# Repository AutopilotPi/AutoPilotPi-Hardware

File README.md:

# [ENGLISH](https://github.com/Ncerzzk/AutoPilotPi-Hardware/blob/master/README_EN.md)
# AutoPilotPi-Hardware

AutoPilotPi 是一个能够运行 PX4 等自动驾驶固件的单板计算机(SBC)。与通用的 SBC（如树莓派）不同，AutoPilotPi 集成了多种传感器（IMU、磁罗盘、气压计等），因此无需额外的接线即可使用，对于微型飞行器和电路洁癖患者来说非常友好。

AutoPilotPi 使用 V3s 处理器，虽然 V3s 不是性能强大的处理器，但如果能够证明 PX4 能在这些性能较弱的 Linux 处理器上运行，则对于性能更强的处理器来说更加不在话下了。

与传统基于 MCU 的自动驾驶固件不同，使用 Linux 系统的优势在于支持更多的开发语言和工具链，可以更方便地进行二次开发和调试。同时，开启了软实时后的内核基本可以满足 PX4 的实时性要求。

## 接口与传感器

- ICM20600：六轴惯性测量单元
- QMC5883L：三轴磁罗盘
- SPL06：气压高度传感器
- 3 个串口(U0、U1、U2，其中 U0 用于 Linux 调试)
- 1 个 I2C 接口
- 1 个 SPI 接口
- 最多 9 个 PWM 通道

## 特点

- 封装对手焊友好 (EQFP-128)
- 内置 DRAM
- 价格较为便宜

## 相关项目

- V3s 的 Linux 内核：https://github.com/Ncerzzk/linux
- 使用该项目的四旋翼飞行器 (WIP)：https://github.com/Ncerzzk/V3s_Quadrotor
- 该项目的 PX4 分支（部分提交尚未被官方 PX4 接受）：https://github.com/Ncerzzk/PX4-Autopilot
- FPGA 的 HDL 代码：https://github.com/Ncerzzk/I2C_PWM
- Wiki：https://github.com/Ncerzzk/AutoPilotPi-Hardware/wiki

## Images

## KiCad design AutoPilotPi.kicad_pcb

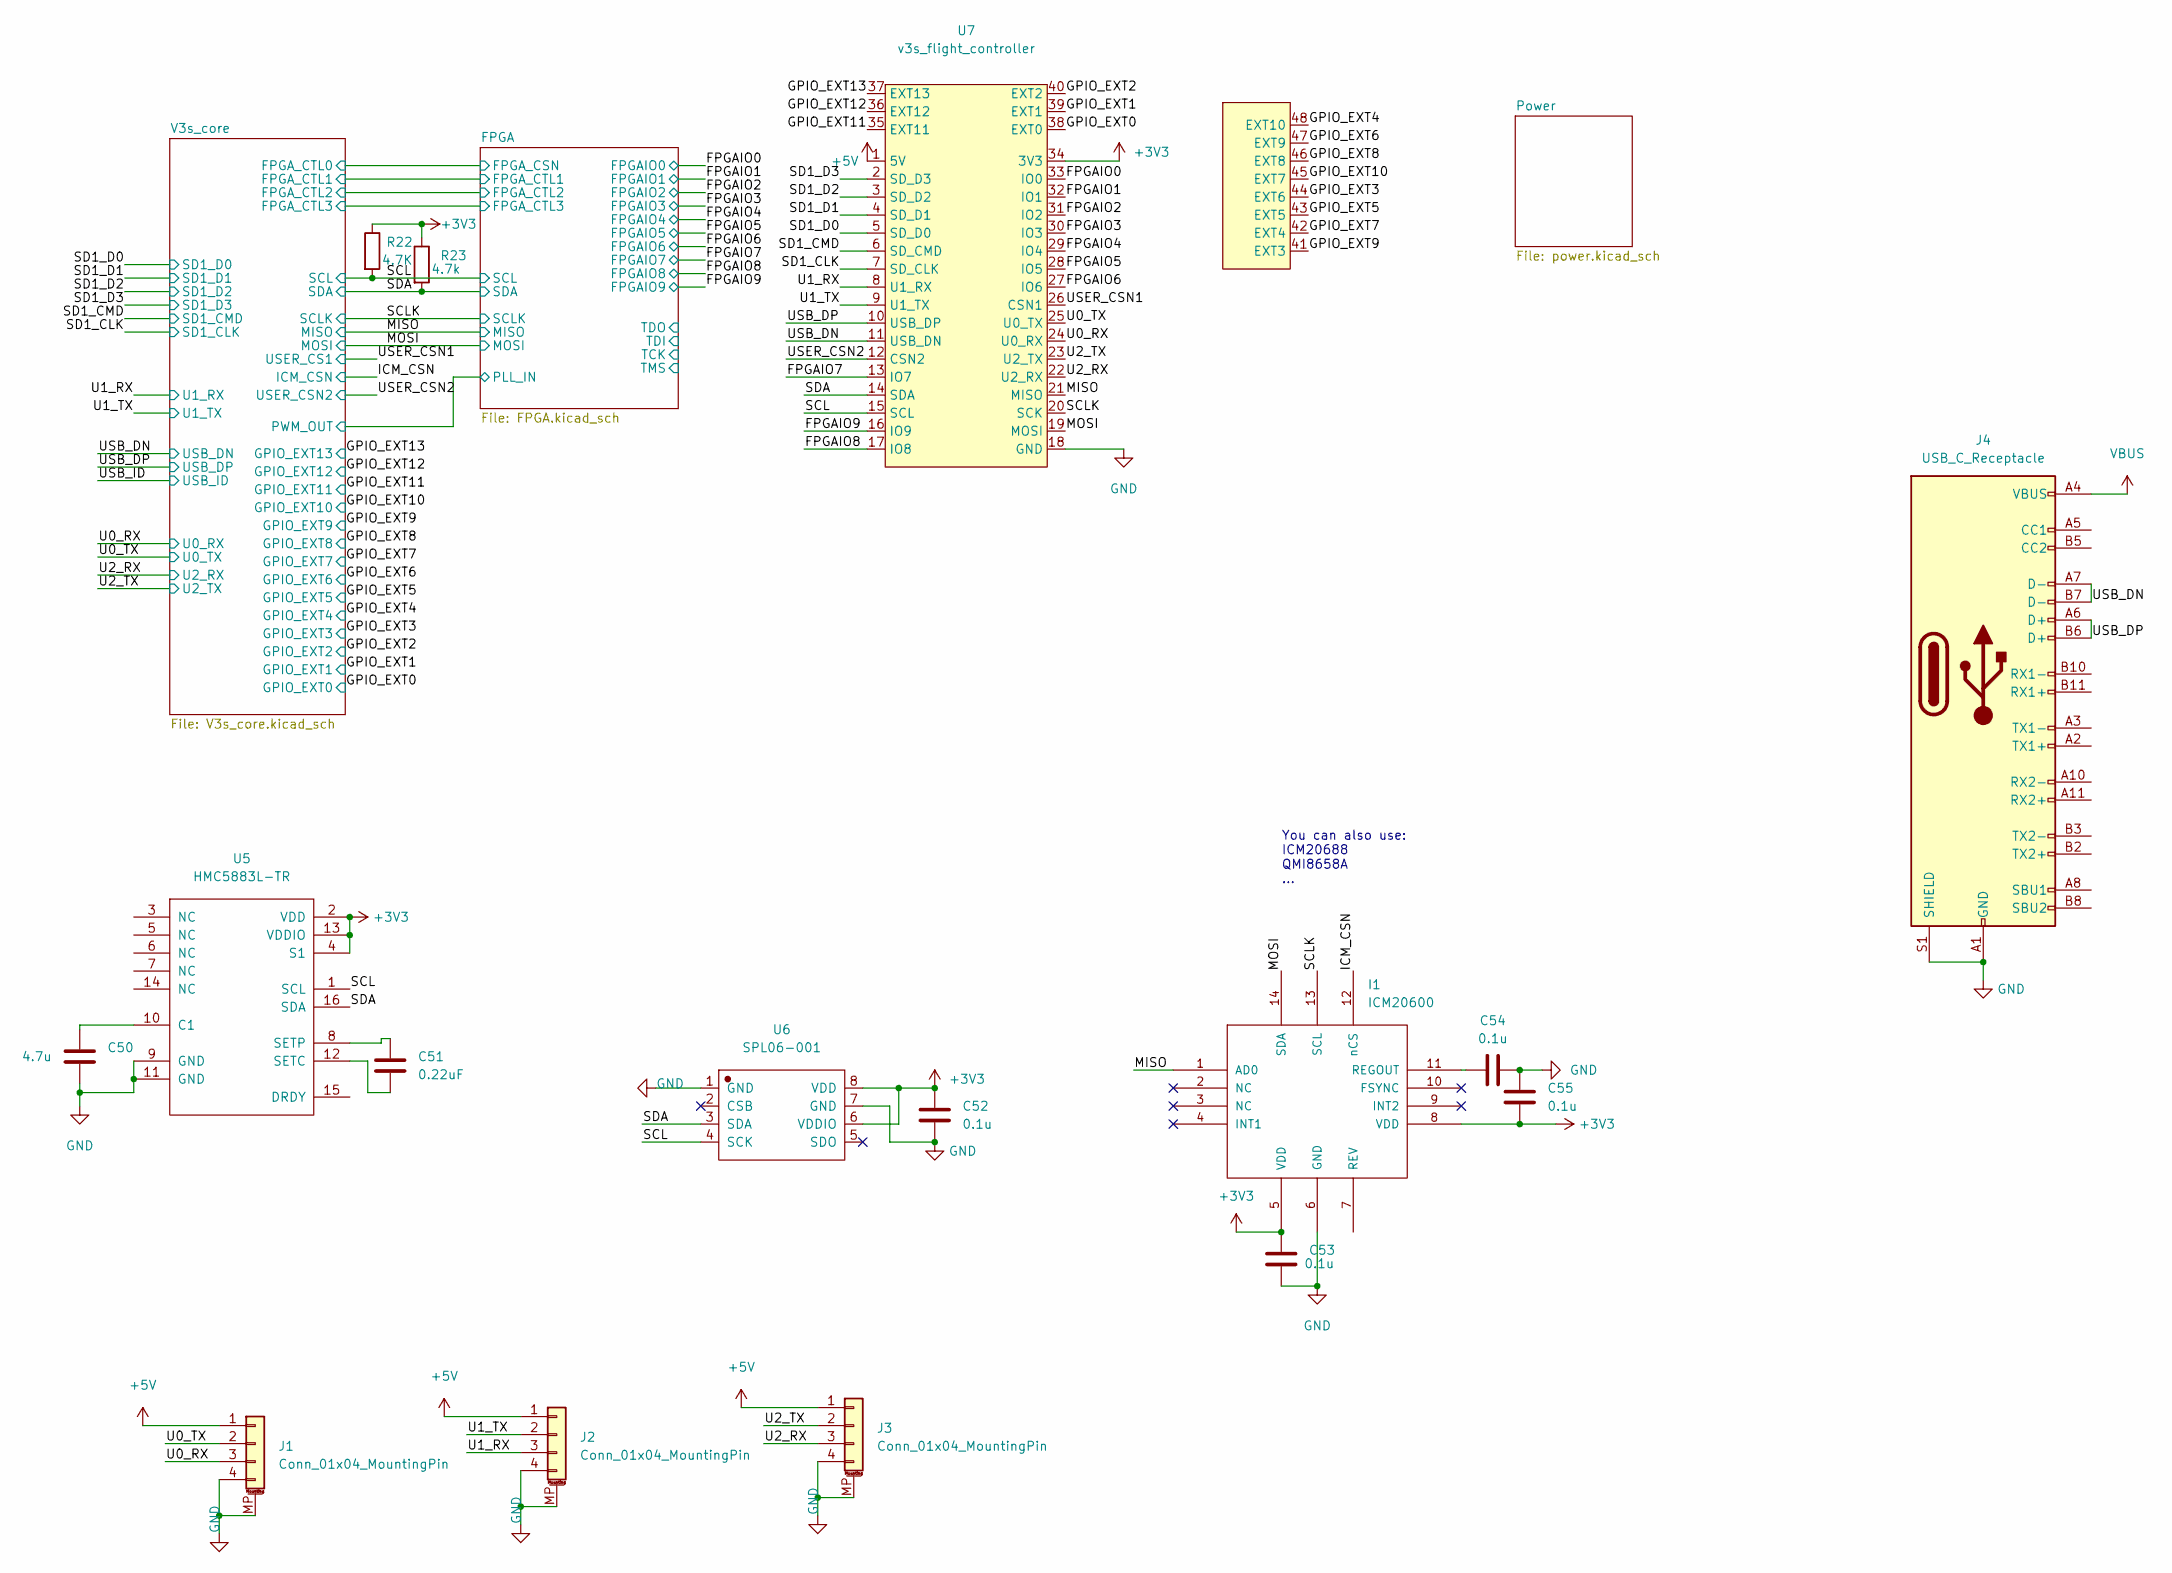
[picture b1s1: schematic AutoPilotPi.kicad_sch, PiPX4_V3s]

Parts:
C50: 4.7u; C_0402_1005Metric
C51: 0.22uF; C_0402_1005Metric
C52, C53, C54, C55: 0.1u; C_0402_1005Metric
I1: ICM20600; Bosch_LGA-14_3x2.5mm_P0.5mm
J1, J2, J3: Conn_01x04_MountingPin; Molex_CLIK-Mate_502382-0470_1x04-1MP_P1.25mm_Vertical
J4: USB_C_Receptacle; USB_C_Receptacle_Palconn_UTC16-G
R22: 4.7K; R_0402_1005Metric
R23: 4.7k; R_0402_1005Metric
U5: HMC5883L-TR; LGA-16_3x3mm_P0.5mm
U6: SPL06-001; Bosch_LGA-8_2x2.5mm_P0.65mm_ClockwisePinNumbering
U7: v3s_flight_controller; Flight_Core

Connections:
+3V3: C52.1, C53.2, C55.2, I1.5 (VDD), I1.8 (VDD), R22.1, R23.1, U5.2 (VDD), U5.4 (S1), U5.13 (VDDIO), U6.6 (VDDIO), U6.8 (VDD), U7.34 (3V3); also elsewhere on the board
+5V: J1.1, J2.1, J3.1, U7.1 (5V); also elsewhere on the board
/FPGAIO0: U7.33 (IO0); also elsewhere on the board
/FPGAIO1: U7.32 (IO1); also elsewhere on the board
/FPGAIO2: U7.31 (IO2); also elsewhere on the board
/FPGAIO3: U7.30 (IO3); also elsewhere on the board
/FPGAIO4: U7.29 (IO4); also elsewhere on the board
/FPGAIO5: U7.28 (IO5); also elsewhere on the board
/FPGAIO6: U7.27 (IO6); also elsewhere on the board
/FPGAIO7: U7.13 (IO7); also elsewhere on the board
/FPGAIO8: U7.17 (IO8); also elsewhere on the board
/FPGAIO9: U7.16 (IO9); also elsewhere on the board
/GPIO_EXT0: U7.38 (EXT0); also elsewhere on the board
/GPIO_EXT1: U7.39 (EXT1); also elsewhere on the board
/GPIO_EXT2: U7.40 (EXT2); also elsewhere on the board
/GPIO_EXT3: U7.44 (EXT6); also elsewhere on the board
/GPIO_EXT4: U7.48 (EXT10); also elsewhere on the board
/GPIO_EXT5: U7.43 (EXT5); also elsewhere on the board
/GPIO_EXT6: U7.47 (EXT9); also elsewhere on the board
/GPIO_EXT7: U7.42 (EXT4); also elsewhere on the board
/GPIO_EXT8: U7.46 (EXT8); also elsewhere on the board
/GPIO_EXT9: U7.41 (EXT3); also elsewhere on the board
/GPIO_EXT10: U7.45 (EXT7); also elsewhere on the board
/GPIO_EXT11: U7.35 (EXT11); also elsewhere on the board
/GPIO_EXT12: U7.36 (EXT12); also elsewhere on the board
/GPIO_EXT13: U7.37 (EXT13); also elsewhere on the board
/ICM_CSN: I1.12 (nCS); also elsewhere on the board
/MISO: I1.1 (AD0), U7.21 (MISO); also elsewhere on the board
/MOSI: I1.14 (SDA), U7.19 (MOSI); also elsewhere on the board
/SCL: R22.2, U5.1 (SCL), U6.4 (SCK), U7.15 (SCL); also elsewhere on the board
/SCLK: I1.13 (SCL), U7.20 (SCK); also elsewhere on the board
/SD1_CLK: U7.7 (SD_CLK); also elsewhere on the board
/SD1_CMD: U7.6 (SD_CMD); also elsewhere on the board
/SD1_D0: U7.5 (SD_D0); also elsewhere on the board
/SD1_D1: U7.4 (SD_D1); also elsewhere on the board
/SD1_D2: U7.3 (SD_D2); also elsewhere on the board
/SD1_D3: U7.2 (SD_D3); also elsewhere on the board
/SDA: R23.2, U5.16 (SDA), U6.3 (SDA), U7.14 (SDA); also elsewhere on the board
/U0_RX: J1.3, U7.24 (U0_RX); also elsewhere on the board
/U0_TX: J1.2, U7.25 (U0_TX); also elsewhere on the board
/U1_RX: J2.3, U7.8 (U1_RX); also elsewhere on the board
/U1_TX: J2.2, U7.9 (U1_TX); also elsewhere on the board
/U2_RX: J3.3, U7.22 (U2_RX); also elsewhere on the board
/U2_TX: J3.2, U7.23 (U2_TX); also elsewhere on the board
/USB_DN: J4.A7 (D-), J4.B7 (D-), U7.11 (USB_DN); also elsewhere on the board
/USB_DP: J4.A6 (D+), J4.B6 (D+), U7.10 (USB_DP); also elsewhere on the board
/USER_CSN1: U7.26 (CSN1); also elsewhere on the board
/USER_CSN2: U7.12 (CSN2); also elsewhere on the board
GND: C50.2, C52.2, C53.1, C54.1, C55.1, I1.6 (GND), J1.4, J1.MP (MountPin), J2.4, J2.MP (MountPin), J3.4, J3.MP (MountPin), J4.A1 (GND), J4.A12 (GND), J4.B1 (GND), J4.B12 (GND), J4.S1 (SHIELD), U5.9 (GND), U5.11 (GND), U6.1 (GND), U6.7 (GND), U7.18 (GND); also elsewhere on the board
unnamed: C50.1, U5.10 (C1)
unnamed: C51.1, U5.8 (SETP)
unnamed: C51.2, U5.12 (SETC)
unnamed: C54.2, I1.11 (REGOUT)
VBUS: J4.A4 (VBUS), J4.A9 (VBUS), J4.B4 (VBUS), J4.B9 (VBUS); also elsewhere on the board

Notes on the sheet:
You can also use: ICM20688 QMI8658A ...

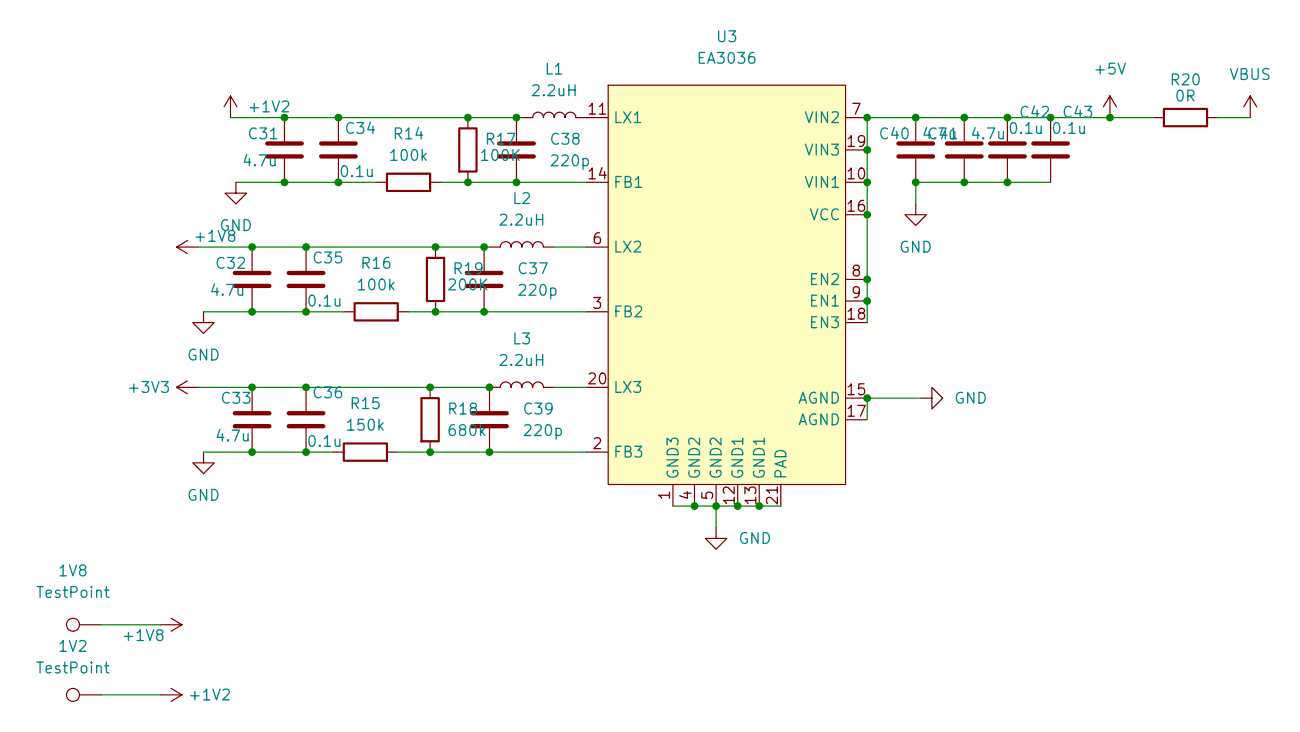
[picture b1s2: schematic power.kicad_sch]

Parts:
1V2, 1V8: TestPoint; TestPoint_Pad_1.0x1.0mm
C31, C32, C33, C40, C41: 4.7u; C_0402_1005Metric
C34, C35, C36, C42, C43: 0.1u; C_0402_1005Metric
C37, C38, C39: 220p; C_0402_1005Metric
L1, L2, L3: 2.2uH; L_Abracon_ASPI-3012S
R14, R16: 100k; R_0402_1005Metric
R15: 150k; R_0402_1005Metric
R17: 100K; R_0402_1005Metric
R18: 680k; R_0402_1005Metric
R19: 200K; R_0402_1005Metric
R20: 0R; R_0402_1005Metric
U3: EA3036; QFN-20-1EP_3x3mm_P0.4mm_EP1.65x1.65mm

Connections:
+1V2: 1V2.1, C31.1, C34.1, C38.1, L1.1, R17.1; also elsewhere on the board
+1V8: 1V8.1, C32.1, C35.1, C37.1, L2.1, R19.1; also elsewhere on the board
+3V3: C33.1, C36.1, C39.1, L3.1, R18.1; also elsewhere on the board
+5V: C40.1, C41.1, C42.1, C43.1, R20.1, U3.7 (VIN2), U3.8 (EN2), U3.9 (EN1), U3.10 (VIN1), U3.16 (VCC), U3.18 (EN3), U3.19 (VIN3); also elsewhere on the board
GND: C31.2, C32.2, C33.2, C34.2, C35.2, C36.2, C40.2, C41.2, C42.2, C43.2, R14.1, R15.1, R16.1, U3.1 (GND3), U3.4 (GND2), U3.5 (GND2), U3.12 (GND1), U3.13 (GND1), U3.15 (AGND), U3.17 (AGND), U3.21 (PAD); also elsewhere on the board
unnamed: C37.2, R16.2, R19.2, U3.3 (FB2)
unnamed: C38.2, R14.2, R17.2, U3.14 (FB1)
unnamed: C39.2, R15.2, R18.2, U3.2 (FB3)
unnamed: L1.2, U3.11 (LX1)
unnamed: L2.2, U3.6 (LX2)
unnamed: L3.2, U3.20 (LX3)
VBUS: R20.2; also elsewhere on the board

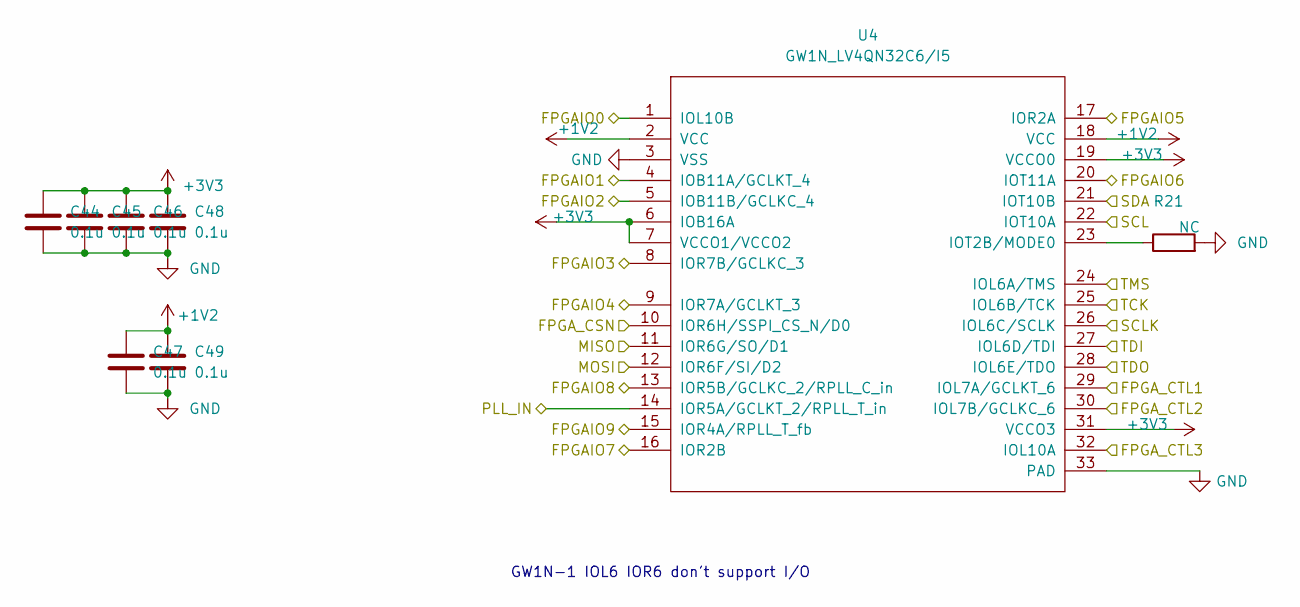
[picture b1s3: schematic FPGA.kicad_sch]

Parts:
C44, C45, C46, C47, C48, C49: 0.1u; C_0402_1005Metric
R21: NC; R_0402_1005Metric
U4: GW1N_LV4QN32C6/I5; QFN-32-1EP_5x5mm_P0.5mm_EP3.45x3.45mm

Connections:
+1V2: C47.1, C49.1, U4.2 (VCC), U4.18 (VCC); also elsewhere on the board
+3V3: C44.1, C45.1, C46.1, C48.1, U4.6 (IOB16A), U4.7 (VCCO1/VCCO2), U4.19 (VCCO0), U4.31 (VCCO3); also elsewhere on the board
/FPGA/FPGA_CSN: U4.10 (IOR6H/SSPI_CS_N/D0); also elsewhere on the board
/FPGA/FPGA_CTL1: U4.29 (IOL7A/GCLKT_6); also elsewhere on the board
/FPGA/FPGA_CTL2: U4.30 (IOL7B/GCLKC_6); also elsewhere on the board
/FPGA/FPGA_CTL3: U4.32 (IOL10A); also elsewhere on the board
/FPGA/PLL_IN: U4.14 (IOR5A/GCLKT_2/RPLL_T_in); also elsewhere on the board
/FPGA/TCK: U4.25 (IOL6B/TCK)
/FPGA/TDI: U4.27 (IOL6D/TDI)
/FPGA/TDO: U4.28 (IOL6E/TDO)
/FPGA/TMS: U4.24 (IOL6A/TMS)
/FPGAIO0: U4.1 (IOL10B); also elsewhere on the board
/FPGAIO1: U4.4 (IOB11A/GCLKT_4); also elsewhere on the board
/FPGAIO2: U4.5 (IOB11B/GCLKC_4); also elsewhere on the board
/FPGAIO3: U4.8 (IOR7B/GCLKC_3); also elsewhere on the board
/FPGAIO4: U4.9 (IOR7A/GCLKT_3); also elsewhere on the board
/FPGAIO5: U4.17 (IOR2A); also elsewhere on the board
/FPGAIO6: U4.20 (IOT11A); also elsewhere on the board
/FPGAIO7: U4.16 (IOR2B); also elsewhere on the board
/FPGAIO8: U4.13 (IOR5B/GCLKC_2/RPLL_C_in); also elsewhere on the board
/FPGAIO9: U4.15 (IOR4A/RPLL_T_fb); also elsewhere on the board
/MISO: U4.11 (IOR6G/SO/D1); also elsewhere on the board
/MOSI: U4.12 (IOR6F/SI/D2); also elsewhere on the board
/SCL: U4.22 (IOT10A); also elsewhere on the board
/SCLK: U4.26 (IOL6C/SCLK); also elsewhere on the board
/SDA: U4.21 (IOT10B); also elsewhere on the board
GND: C44.2, C45.2, C46.2, C47.2, C48.2, C49.2, R21.2, U4.3 (VSS), U4.33 (PAD); also elsewhere on the board
unnamed: R21.1, U4.23 (IOT2B/MODE0)

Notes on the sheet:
GW1N-1 IOL6 IOR6 don't support I/O

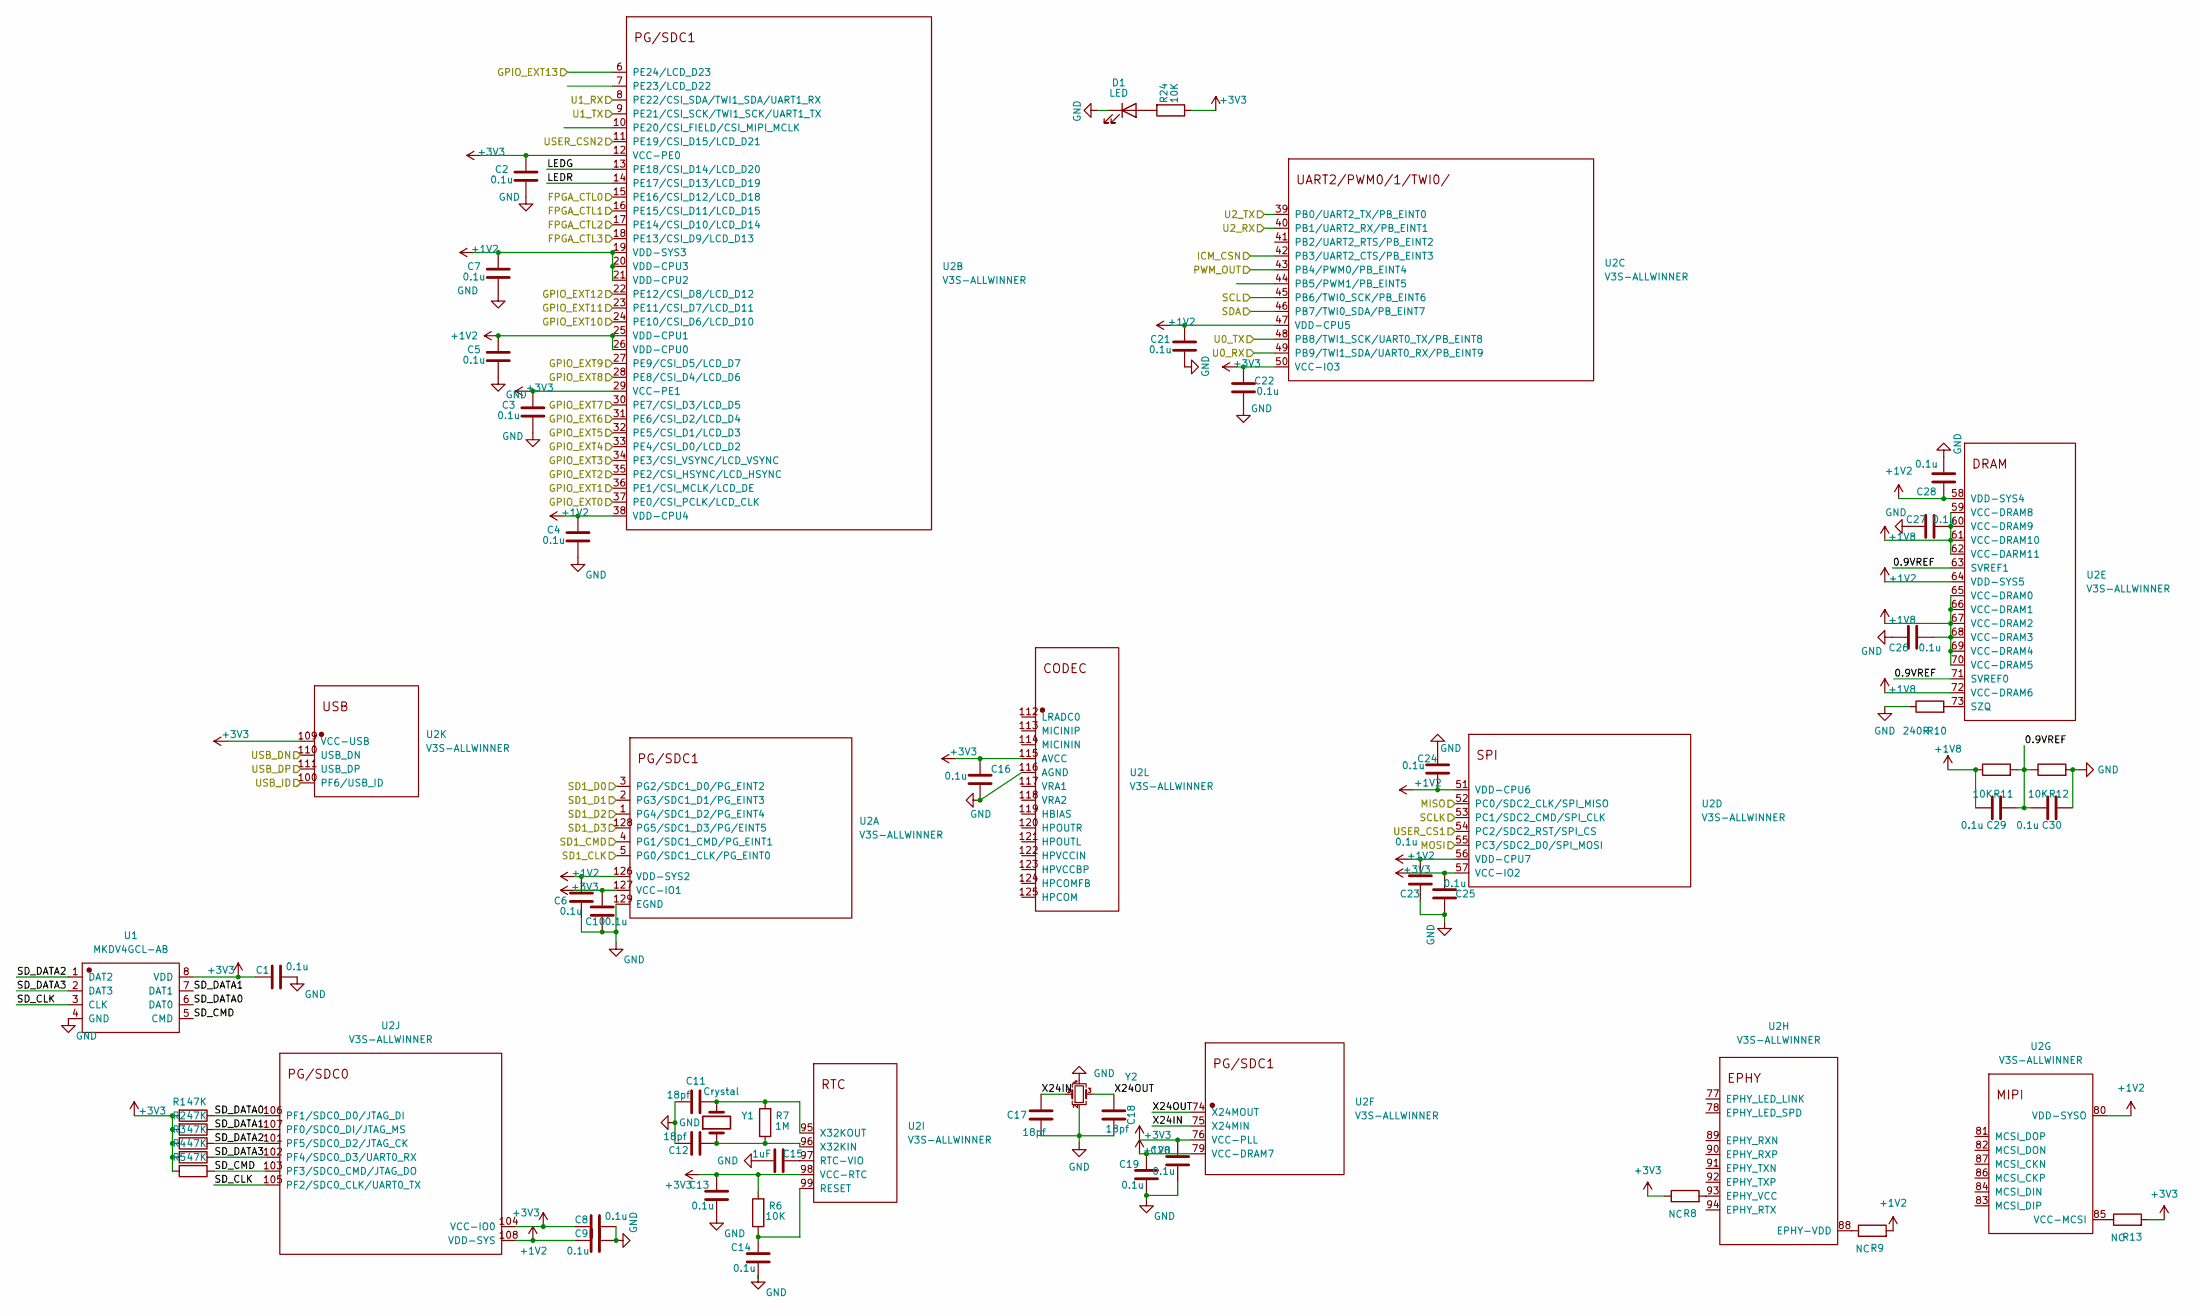
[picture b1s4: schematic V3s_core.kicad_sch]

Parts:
C1, C2, C3, C4, C5, C6, C7, C8, C9, C10, C13, C14, C16, C19, C20, C21, C22, C23, C24, C25, C26, C27, C28, C29, C30: 0.1u; C_0402_1005Metric
C11, C12, C17, C18: 18pf; C_0402_1005Metric
C15: 1uF; C_0402_1005Metric
D1: LED; LED_0603_1608Metric
R1, R2, R3, R4, R5: 47K; R_0402_1005Metric
R6, R11, R12, R24: 10K; R_0402_1005Metric
R7: 1M; R_0402_1005Metric
R8, R9, R13: NC; R_0402_1005Metric
R10: 240R; R_0402_1005Metric
U1: MKDV4GCL-AB; LGA-8_L8.0-W6.0-BL_MKDV4GIL-AS
U2: V3S-ALLWINNER; EQFP-128_14x14mm_P0.4mm
Y1: Crystal; Crystal_SMD_3215-2Pin_3.2x1.5mm
Y2: Crystal_GND24_Small; Crystal_SMD_EuroQuartz_MT-4Pin_3.2x2.5mm

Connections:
+1V2: C4.1, C5.1, C6.1, C7.1, C9.2, C21.1, C23.1, C24.2, C28.2, R9.2, U2.19 (VDD-SYS3), U2.20 (VDD-CPU3), U2.21 (VDD-CPU2), U2.25 (VDD-CPU1), U2.26 (VDD-CPU0), U2.38 (VDD-CPU4), U2.47 (VDD-CPU5), U2.51 (VDD-CPU6), U2.56 (VDD-CPU7), U2.58 (VDD-SYS4), U2.64 (VDD-SYS5), U2.80 (VDD-SYSO), U2.108 (VDD-SYS), U2.126 (VDD-SYS2); also elsewhere on the board
+1V8: C19.2, C26.1, C27.1, C29.1, R11.1, U2.59 (VCC-DRAM8), U2.60 (VCC-DRAM9), U2.61 (VCC-DRAM10), U2.62 (VCC-DARM11), U2.65 (VCC-DRAM0), U2.66 (VCC-DRAM1), U2.67 (VCC-DRAM2), U2.68 (VCC-DRAM3), U2.69 (VCC-DRAM4), U2.70 (VCC-DRAM5), U2.72 (VCC-DRAM6), U2.79 (VCC-DRAM7); also elsewhere on the board
+3V3: C1.2, C2.1, C3.1, C8.2, C10.1, C13.2, C16.1, C20.2, C22.1, C25.1, R1.2, R2.2, R3.2, R4.2, R5.2, R6.2, R8.1, R13.2, R24.1, U1.8 (VDD), U2.12 (VCC-PE0), U2.29 (VCC-PE1), U2.50 (VCC-IO3), U2.57 (VCC-IO2), U2.76 (VCC-PLL), U2.98 (VCC-RTC), U2.104 (VCC-IO0), U2.109 (VCC-USB), U2.115 (AVCC), U2.127 (VCC-IO1); also elsewhere on the board
/FPGA/FPGA_CSN: U2.15 (PE16/CSI_D12/LCD_D18); also elsewhere on the board
/FPGA/FPGA_CTL1: U2.16 (PE15/CSI_D11/LCD_D15); also elsewhere on the board
/FPGA/FPGA_CTL2: U2.17 (PE14/CSI_D10/LCD_D14); also elsewhere on the board
/FPGA/FPGA_CTL3: U2.18 (PE13/CSI_D9/LCD_D13); also elsewhere on the board
/FPGA/PLL_IN: U2.43 (PB4/PWM0/PB_EINT4); also elsewhere on the board
/GPIO_EXT0: U2.37 (PE0/CSI_PCLK/LCD_CLK); also elsewhere on the board
/GPIO_EXT1: U2.36 (PE1/CSI_MCLK/LCD_DE); also elsewhere on the board
/GPIO_EXT2: U2.35 (PE2/CSI_HSYNC/LCD_HSYNC); also elsewhere on the board
/GPIO_EXT3: U2.34 (PE3/CSI_VSYNC/LCD_VSYNC); also elsewhere on the board
/GPIO_EXT4: U2.33 (PE4/CSI_D0/LCD_D2); also elsewhere on the board
/GPIO_EXT5: U2.32 (PE5/CSI_D1/LCD_D3); also elsewhere on the board
/GPIO_EXT6: U2.31 (PE6/CSI_D2/LCD_D4); also elsewhere on the board
/GPIO_EXT7: U2.30 (PE7/CSI_D3/LCD_D5); also elsewhere on the board
/GPIO_EXT8: U2.28 (PE8/CSI_D4/LCD_D6); also elsewhere on the board
/GPIO_EXT9: U2.27 (PE9/CSI_D5/LCD_D7); also elsewhere on the board
/GPIO_EXT10: U2.24 (PE10/CSI_D6/LCD_D10); also elsewhere on the board
/GPIO_EXT11: U2.23 (PE11/CSI_D7/LCD_D11); also elsewhere on the board
/GPIO_EXT12: U2.22 (PE12/CSI_D8/LCD_D12); also elsewhere on the board
/GPIO_EXT13: U2.6 (PE24/LCD_D23); also elsewhere on the board
/ICM_CSN: U2.42 (PB3/UART2_CTS/PB_EINT3); also elsewhere on the board
/MISO: U2.52 (PC0/SDC2_CLK/SPI_MISO); also elsewhere on the board
/MOSI: U2.55 (PC3/SDC2_D0/SPI_MOSI); also elsewhere on the board
/SCL: U2.45 (PB6/TWI0_SCK/PB_EINT6); also elsewhere on the board
/SCLK: U2.53 (PC1/SDC2_CMD/SPI_CLK); also elsewhere on the board
/SD1_CLK: U2.5 (PG0/SDC1_CLK/PG_EINT0); also elsewhere on the board
/SD1_CMD: U2.4 (PG1/SDC1_CMD/PG_EINT1); also elsewhere on the board
/SD1_D0: U2.3 (PG2/SDC1_D0/PG_EINT2); also elsewhere on the board
/SD1_D1: U2.2 (PG3/SDC1_D1/PG_EINT3); also elsewhere on the board
/SD1_D2: U2.1 (PG4/SDC1_D2/PG_EINT4); also elsewhere on the board
/SD1_D3: U2.128 (PG5/SDC1_D3/PG/EINT5); also elsewhere on the board
/SDA: U2.46 (PB7/TWI0_SDA/PB_EINT7); also elsewhere on the board
/U0_RX: U2.49 (PB9/TWI1_SDA/UART0_RX/PB_EINT9); also elsewhere on the board
/U0_TX: U2.48 (PB8/TWI1_SCK/UART0_TX/PB_EINT8); also elsewhere on the board
/U1_RX: U2.8 (PE22/CSI_SDA/TWI1_SDA/UART1_RX); also elsewhere on the board
/U1_TX: U2.9 (PE21/CSI_SCK/TWI1_SCK/UART1_TX); also elsewhere on the board
/U2_RX: U2.40 (PB1/UART2_RX/PB_EINT1); also elsewhere on the board
/U2_TX: U2.39 (PB0/UART2_TX/PB_EINT0); also elsewhere on the board
/USB_DN: U2.110 (USB_DN); also elsewhere on the board
/USB_DP: U2.111 (USB_DP); also elsewhere on the board
/USB_ID: U2.100 (PF6/USB_ID)
/USER_CSN1: U2.54 (PC2/SDC2_RST/SPI_CS); also elsewhere on the board
/USER_CSN2: U2.11 (PE19/CSI_D15/LCD_D21); also elsewhere on the board
/V3s_core/0.9VREF: C29.2, C30.1, R11.2, R12.1, U2.63 (SVREF1), U2.71 (SVREF0)
/V3s_core/LEDG: U2.13 (PE18/CSI_D14/LCD_D20)
/V3s_core/LEDR: U2.14 (PE17/CSI_D13/LCD_D19)
/V3s_core/SD_CLK: U1.3 (CLK), U2.105 (PF2/SDC0_CLK/UART0_TX)
/V3s_core/SD_CMD: R5.1, U1.5 (CMD), U2.103 (PF3/SDC0_CMD/JTAG_DO)
/V3s_core/SD_DATA0: R1.1, U1.6 (DAT0), U2.106 (PF1/SDC0_D0/JTAG_DI)
/V3s_core/SD_DATA1: R2.1, U1.7 (DAT1), U2.107 (PF0/SDC0_DI/JTAG_MS)
/V3s_core/SD_DATA2: R3.1, U1.1 (DAT2), U2.101 (PF5/SDC0_D2/JTAG_CK)
/V3s_core/SD_DATA3: R4.1, U1.2 (DAT3), U2.102 (PF4/SDC0_D3/UART0_RX)
/V3s_core/X24IN: C17.2, U2.75 (X24MIN), Y2.1
/V3s_core/X24OUT: C18.2, U2.74 (X24MOUT), Y2.3
GND: C1.1, C2.2, C3.2, C4.2, C5.2, C6.2, C7.2, C8.1, C9.1, C10.2, C11.1, C12.1, C13.1, C14.1, C15.1, C16.2, C17.1, C18.1, C19.1, C20.1, C21.2, C22.2, C23.2, C24.1, C25.2, C26.2, C27.2, C28.1, C30.2, D1.1 (K), R10.1, R12.2, U1.4 (GND), U2.116 (AGND), U2.129 (EGND), Y2.2, Y2.4; also elsewhere on the board
unnamed: C11.2, R7.2, U2.95 (X32KOUT), Y1.2
unnamed: C12.2, R7.1, U2.96 (X32KIN), Y1.1
unnamed: C14.2, R6.1, U2.99 (RESET)
unnamed: C15.2, U2.97 (RTC-VIO)
unnamed: D1.2 (A), R24.2
unnamed: R8.2, U2.93 (EPHY_VCC)
unnamed: R9.1, U2.88 (EPHY-VDD)
unnamed: R10.2, U2.73 (SZQ)
unnamed: R13.1, U2.85 (VCC-MCSI)

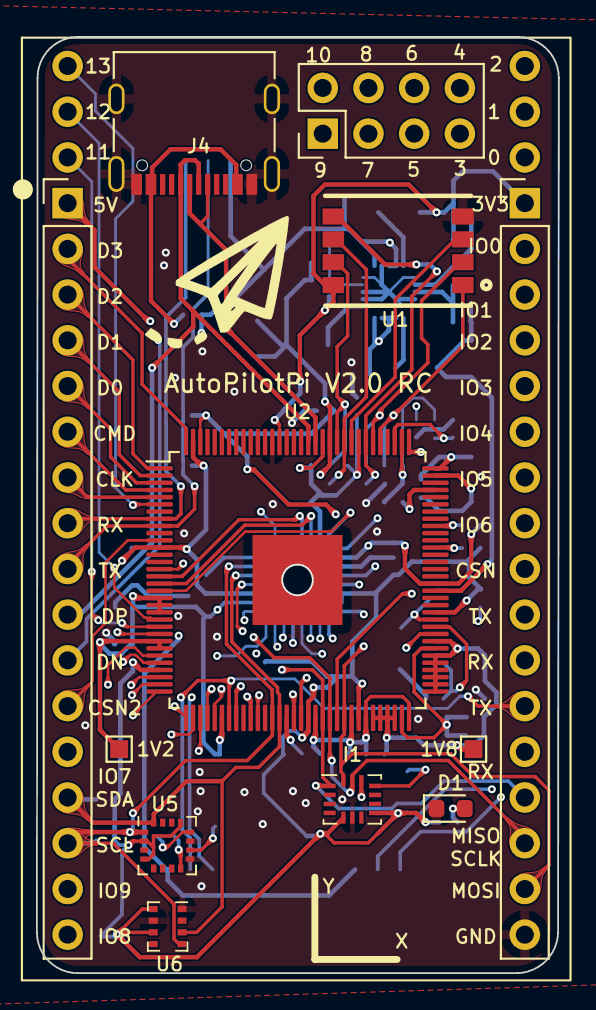
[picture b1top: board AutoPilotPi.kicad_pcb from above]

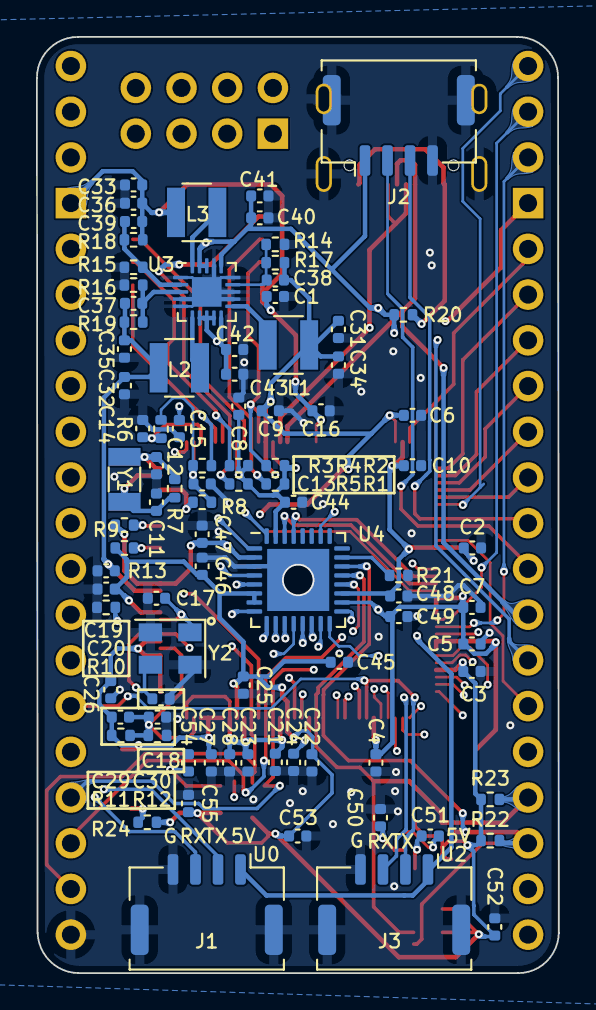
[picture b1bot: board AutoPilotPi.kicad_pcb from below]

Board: 4 copper layers, 29.0 x 52.0 mm, 99 parts (89 on the bottom side), 86 nets.

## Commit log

2022-03-27 init
2022-03-27 add docs and images
2022-03-27 add teardrop, change the size of drill to 0.45mm
2022-03-30 edit spacing to 0.999mm because of JLC
2022-04-12 fix u0_rx u0_tx wrong connection issue, fix the hole in V3s GND PAD is too small issue. update to V0.95.
2022-04-16 use LDO to produce 1.2V, to fix fpga voltage issue. fix wrong fpga sch issue, change the pins of fpga. connect fpga SSPI to V3s-spi, so that we can configuare fpag on v3s someday.
2022-04-16 update docs, images, readme
2022-05-15 add gowin dir, add gowin.c to support HOST sram config(SSPI)
2022-05-23 Rename README.md to README_EN.md
2022-06-16 v1.0
2022-06-25 add wiki in Readme
2022-07-08 update mini
2022-09-07 v2.0-devel init
2022-09-08 temply update
2022-09-17 update images for mini
2022-09-17 update readme for images url
2023-02-11 add esp32 as wifi card
2023-02-11 edit images
2023-09-24 update images
